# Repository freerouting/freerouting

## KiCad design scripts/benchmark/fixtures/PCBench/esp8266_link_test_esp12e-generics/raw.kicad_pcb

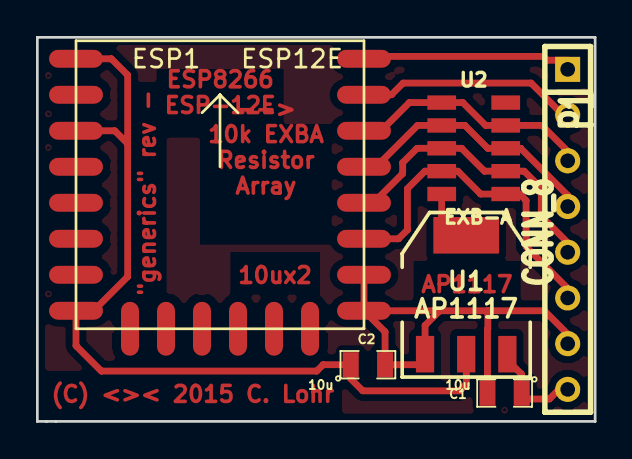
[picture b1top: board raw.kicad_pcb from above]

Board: 2 copper layers, 31.0 x 21.3 mm, 6 parts (0 on the bottom side), 10 nets.

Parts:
C1, C2: 10u; SM0805
ESP1: ESP12E
P1: CONN_8; SIL-8
U1: AP1117; SOT223
U2: EXB-A

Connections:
+3.3V: C2.1, ESP1.1, ESP1.3, ESP1.8, U1.2
+5V: C1.1, P1.8, U1.3
GND: C1.2, C2.2, ESP1.15, ESP1.16, P1.7, U1.1
GPIO0: ESP1.18, P1.5, U2.3, U2.7
GPIO2: ESP1.17, P1.6, U2.4, U2.6
GPIO4: ESP1.19, P1.4, U2.2, U2.8
GPIO5: ESP1.20, P1.3, U2.1, U2.9
unnamed: U1.4, U2.5
RX: ESP1.21, P1.2
TX: ESP1.22, P1.1

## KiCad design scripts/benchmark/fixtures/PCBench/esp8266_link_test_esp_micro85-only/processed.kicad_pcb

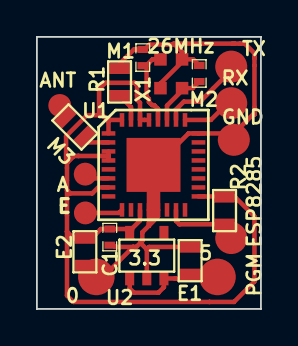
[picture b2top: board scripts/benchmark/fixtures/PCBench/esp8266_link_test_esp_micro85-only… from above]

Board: 2 copper layers, 12.4 x 15.1 mm, 20 parts (0 on the bottom side), 13 nets.

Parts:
C1: .1u; SM0402
E1, E2: 10u; SM0603
M1, M2: 5.6p; SM0402
M3: 5.6p; SM0603
P1: RX; .1SMTPIN
P2: TX; .1SMTPIN
P3: GND; .1SMTPIN
P4: ANT; .1SMTPIN
P5: A; .1SMTPIN
P6: 0; .1SMTPIN
P7: 5; .1SMTPIN
P8: PGM; .1SMTPIN
P9: E; .1SMTPIN
R1, R2: 12k; SM0603
U1: ESP8285; QFN32
U2: 3.3; SOT23-5
X1: 26MHz; XTAL4TINY

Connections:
+3.3V: C1.2, E2.2, R2.1, U1.1, U1.3, U1.4, U1.7, U1.11, U1.17, U1.29, U1.30, U1.32, U2.5
+5V: E1.2, P7.1, U2.1, U2.3
GND: C1.1, E1.1, E2.1, M1.2, M2.2, P3.1, P6.1, R1.1, U1.12, U1.13, U1.24, U1.33, U2.2, X1.3, X1.4
unnamed: P5.1, U1.6
unnamed: P2.1, U1.26
unnamed: P1.1, U1.25
unnamed: P8.1, R2.2, U1.15
unnamed: P9.1, U1.9
unnamed: M1.1, U1.28, X1.1
unnamed: M3.2, U1.2
unnamed: M2.1, U1.27, X1.2
unnamed: R1.2, U1.31
unnamed: M3.1, P4.1

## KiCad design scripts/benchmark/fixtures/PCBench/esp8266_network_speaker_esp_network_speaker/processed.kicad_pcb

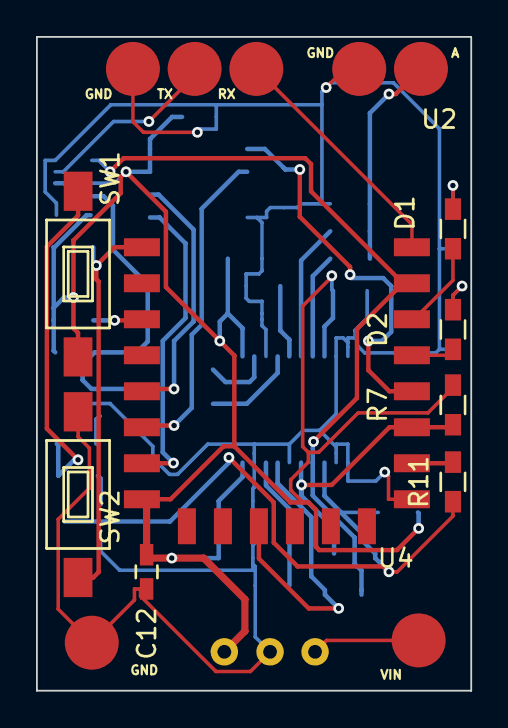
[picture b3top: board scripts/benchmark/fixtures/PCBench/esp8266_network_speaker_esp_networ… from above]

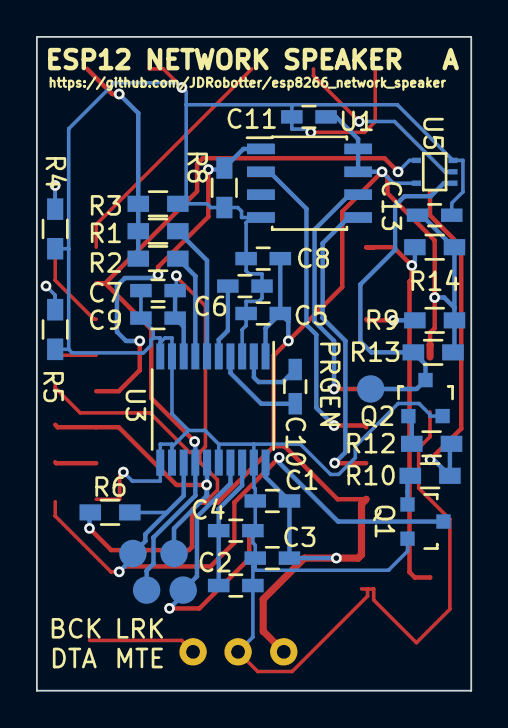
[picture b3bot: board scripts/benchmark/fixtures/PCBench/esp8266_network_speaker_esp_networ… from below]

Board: 2 copper layers, 24.1 x 36.3 mm, 50 parts (34 on the bottom side), 31 nets.

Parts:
BCK: TEST_1P; Measurement_Point_Round-SMD-Pad_Small
C1, C2, C8, C9, C11, C12, C13: 100nF; C_0603_HandSoldering
C3, C4, C5, C7: 10uF; C_0603_HandSoldering
C6, C10: 2.2uF; C_0603_HandSoldering
D1, D2: LED; R_0603_HandSoldering
DTA: TEST_1P; Measurement_Point_Round-SMD-Pad_Small
LRK: TEST_1P; Measurement_Point_Round-SMD-Pad_Small
MTE: TEST_1P; Measurement_Point_Round-SMD-Pad_Small
PRGEN: TEST_1P; Measurement_Point_Round-SMD-Pad_Small
Q1, Q2: Q_NPN_BEC; SOT-23
R1, R2: 470; R_0603_HandSoldering
R3, R6, R7, R8, R9, R13, R14: 10k; R_0603_HandSoldering
R4, R5: 220; R_0603_HandSoldering
R10, R12: 1k; R_0603_HandSoldering
R11: 100; R_0603_HandSoldering
SW1, SW2: SW_PUSH; SW_SPST_FSMSM
U1: 23LC1024; SOIC-8_3.9x4.9mm_Pitch1.27mm
U2: ESP12
U3: PCM5100A; TSSOP-20_4.4x6.5mm_Pitch0.65mm
U4: TSR_1-2433; TSR-1
U5: M74VHC1GT125; SOT-353
W7: AOUT; Measurement_Point_Round-SMD-Pad_Big
W8: AGND; Measurement_Point_Round-SMD-Pad_Big
W9: PBATT; Measurement_Point_Round-SMD-Pad_Big
W10: PGND; Measurement_Point_Round-SMD-Pad_Big
W11: PROG_GND; Measurement_Point_Round-SMD-Pad_Big
W12: PROG_RX; Measurement_Point_Round-SMD-Pad_Big
W13: PROG_TX; Measurement_Point_Round-SMD-Pad_Big

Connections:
+3V3: C1.1, C3.1, C5.1, C7.1, C8.1, C9.1, C11.1, C12.1, C13.1, R6.1, R7.1, R9.2, R13.1, R14.1, SW1.1, U1.7, U1.8, U2.8, U3.1, U3.8, U3.20, U4.3, U5.5
/PROG_EN: PRGEN.1, Q2.3, R13.2, U5.1
/PROG_TX: U5.2, W13.1
/VBATT: U4.1, W9.1
DAC_BCK: BCK.1, Q1.3, R6.2, R11.1, U3.13
DAC_DATA: DTA.1, U2.21, U3.14, U5.4
DAC_LRCK: LRK.1, R7.2, U2.17, U3.15
DAC_MUTE: MTE.1, U2.11, U3.17
DAC_OUTL: R1.2, U3.6
DAC_OUTR: R2.2, U3.7
ESP12_CLK: U1.6, U2.5
ESP12_CS: R8.1, U1.1, U2.18
ESP12_MISO: U1.2, U2.6
ESP12_MOSI: U1.5, U2.7
ESP12_RESET: R14.2, SW2.1, U2.1
ESP12_TX: U2.22, W12.1
GND: C1.2, C2.1, C3.2, C4.2, C5.2, C6.1, C7.2, C8.2, C9.2, C11.2, C12.2, C13.2, Q1.2, Q2.2, R3.2, R4.1, R5.1, R8.2, SW2.2, U1.4, U2.15, U3.3, U3.9, U3.10, U3.11, U3.12, U3.16, U3.19, U4.2, U5.3, W8.1, W10.1, W11.1
LEDA: D2.2, U2.19
LEDB: D1.2, U2.20
unnamed: C2.2, C4.1, U3.18
unnamed: C6.2, U3.5
unnamed: C10.1, U3.2
unnamed: C10.2, U3.4
unnamed: D1.1, R4.2
unnamed: D2.1, R5.2
unnamed: Q1.1, R10.1
unnamed: Q2.1, R12.1
unnamed: R1.1, R2.1, R3.1, W7.1
unnamed: R9.1, U2.3
unnamed: R10.2, R12.2, SW1.2
unnamed: R11.2, U2.16
